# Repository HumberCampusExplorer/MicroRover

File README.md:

# Micro Rover
Adapted from [Rick's Trinket Rover](https://github.com/rwinscot/TrinketRover), estimated build time: 3 hours.

## Table of Contents
1. [Introduction](https://github.com/six0four/MicroRover#1-introduction)
2. [Bill of Materials and Required Tools](https://github.com/six0four/MicroRover#2-bill-of-materials-and-required-tools)
3. [Instructions](https://github.com/six0four/MicroRover#3-instructions)
4. [Future Development](https://github.com/six0four/MicroRover#4-future-development)

## 1. Introduction
A common introduction to microcontrollers is through the [Lego NXT ROBOTC Curriculum](http://www.education.rec.ri.cmu.edu/previews/robot_c_products/teaching_rc_lego_v2_preview/home/ROBOTC_Curriculum_Outline.pdf). This project aims to use a low cost platform to also explore microcontrollers. Similarly, a small rover is assembled as the vehicle. Currently the small rover moves forward until an object reflects infrared light which triggers it to reverse and turn before continuing forward again.

## 2. Bill of Materials and Required Tools
For a list of materials please see the Excel file in the repository.

Regarding tools, the following are a minimum:
- Safety glasses.
- Soldering iron and lead free solder (to be added to materials list).
- Small side cutting pliers.
- Small Phillips screw driver.

## 3. Instructions
1. Soldering guidance:
	1. Start off by watching some ahort soldering guidance videos: [NASA Jove Project](https://radiojove.gsfc.nasa.gov/telescope/soldering.htm).
	2. Continue by watching some [YouTube Videos](https://www.youtube.com/watch?v=BLfXXRfRIzY&list=PLQ32vZrF5U2lFOJTtZDytBWBYVLNp4RYz).
	3. Be sure to wear safety glasses and consult an expert regarding safety, you can even start at your [local hackerspace](https://wiki.hackerspaces.org/List_of_Hackerspaces).
2. Start by programming the trinket with a blink program prior to soldering to make sure it works.
3. Soldering the headers onto to make sure trinket undamaged.
4. Upload the blink program to the trinket again to make sure it is undamaged.
6, Power the trinket from the power supply. Set the current limit.
4. Test the voltage on the 3.7 V 350 mAh Lithium Ion Polymer 552035 Cell. (Notice from the datasheet that the <a href="https://cdn-shop.adafruit.com/product-files/2750/LP552035_350MAH_3.7V_20150906.pdf">Discharge Cut-off
is 3.0V, the Charging Cut-off is 4.2V, and the Storage Voltage is 3.7-3.85V</a>)
7. Turn on the oscilloscope.
8. Turn on the funtion generator.
9. Disconnect the power supply and connect the 
5. Upload the rover code to the trinket.
6.
7.
8.

Fritzing diagrams needed

## 4. Future Development:
- Incorporate multimeter use to check cell.
- Incorporate power supply use as a current controlled alternative to lion cell.
- Incorporate oscilloscope use to view servo motor command signal.
- Incorporate function generator use to create a test control signals.
- Serial communication http://www.ernstc.dk/arduino/tinycom.html to view digitization of infra-red sensor.
- Optimize to stay on desk.
- Optimize to seek dark spaces.
- Optimize for line following.
- Optimize to seek bright spaces and charge via a solar panel.
- Add bluetooth.
- Connect to an Android App that is also connected to Firebase.
- Re-flashing, changing, and removing boot loaders.
- Support for more operating systems.
- Support for more programming languages (Atmel AVR Assembly, ANSI C, Java, Python, IEC 61131-3, javascript, etc.).
- Support for more development environments (AVR-GCC/vi|emacs/AVRdude, Atmel Studio/Visual Studio, etc.).
- Optimize for mapping.
- Communicate with an I2C device as a master
- Communicate with an SPI device.
- Communicate with an I2C device as a slave.
- Communicate with a UART device.
- Communicate via infra-red remote codes.
- Add an H-bridge.
- Add an opto-coupler.
- Add a bidirectional level shifter.
- Modify for DC motors, optical encoders, relays.
- Modify for stepper motors (bipolar and unipolar).
- https://thewanderingengineer.com/2014/08/11/pin-change-interrupts-on-attiny85/
- PID feedback control, fan, thermistor, thermocouple.
- Function generator.
- D to A, PWM.
- A to D, filters.
- Solar cell, photo-resistor.
- Wheatstone bridge, instrumentation amplifier.
- Displays.
- De-bouncing reed switch.
- Emulate a keyboard.
- Playback sound.
- Create a custom PCB with an integrated USB port.
- Shift register, multiplexer.
- RS232, RS485.
- Add a 9-DOF IMU.
- Add MICROCHIP I2C I/O Expander MCP23017.
- Use with http://www.atmel.com/tools/atatmel-ice.aspx and http://www.microchip.com/DevelopmentTools/ProductDetails.aspx?PartNO=ATPOWERDEBUGGER
- Design shell for injection molding.
- Bar/QR code scanners, RFID, magnetic strip, fingerprint readers.
- Add SJA1000/MCP2515 for CAN.
- http://perso.uclouvain.be/fstandae/lightweight_ciphers/
- http://www.instructables.com/id/Optical-Mouse-Odometer-for-Arduino-Robot/?ALLSTEPS
- Currently the project uses a low cost, low power microcontroller from Microchip (Atmel). It could be expanded to be suitable for offerings from other companies such as:
	- Broadcom
	- National Instruments
	- Philips
	- Qualcomm (including NXP, Motorola, and Freescale)
	- Texas Instruments
	- Xilinx
	- Altera
	- Analog Devices
	- Cypress
	- Exynos (Samsung)
	- Infineon Technologies
	- Nordic Semiconductor
	- ON Semiconductor (including Fairchild)
	- Renesas Electronics (including NEC, Hitatchi, Mitsubishi)
	- SGS-THOMSON Microelectronics
	- Silicon Labs

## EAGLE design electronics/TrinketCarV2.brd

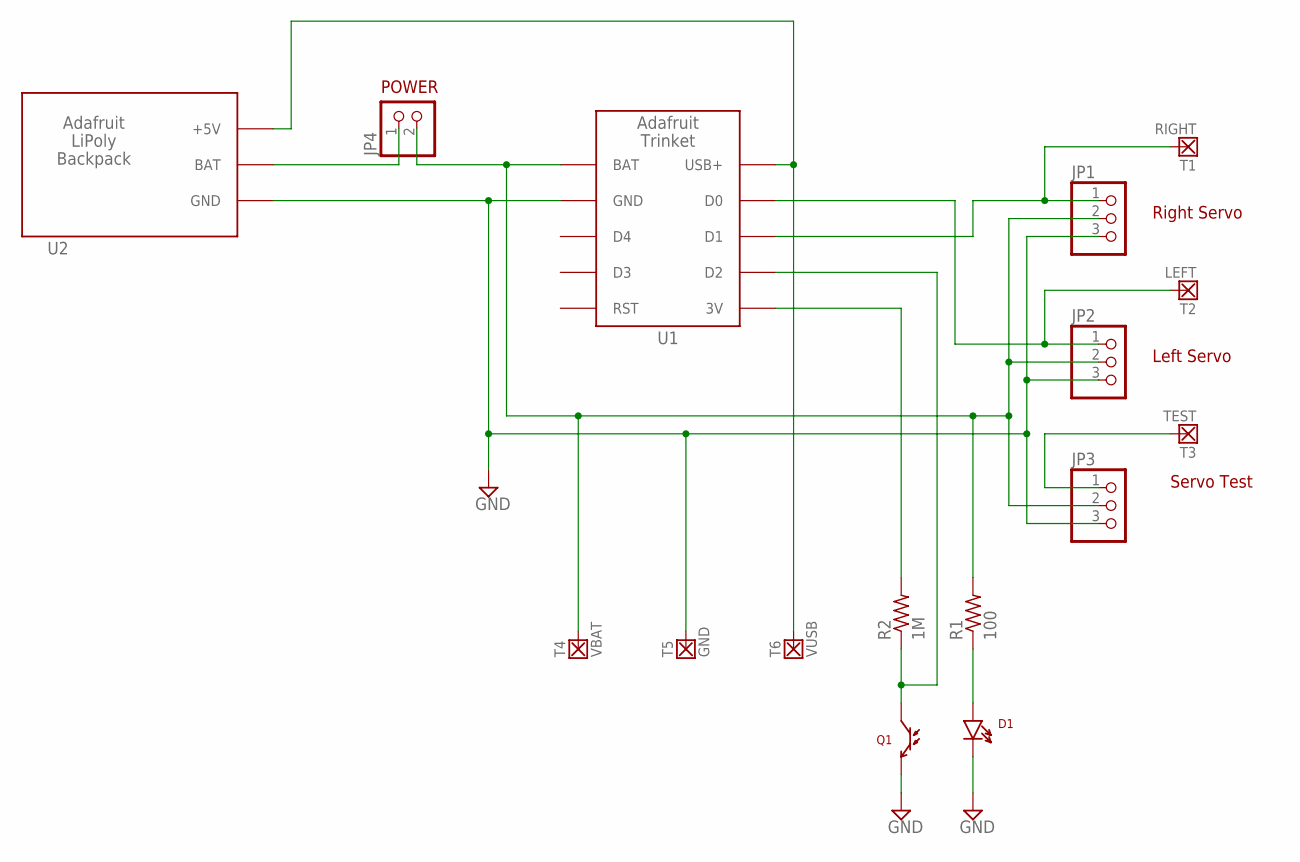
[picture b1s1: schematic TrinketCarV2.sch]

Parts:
D1: LTE-302
JP1, JP2, JP3: PINHD-1X3; 1X03
JP4: PINHD-1X2; 1X02
Q1: LTR-301
R1: 100; 0207/12
R2: 1M; 0207/12
T1: RIGHT; TERMPAD-SMALL
T2: LEFT; TERMPAD-SMALL
T3: TEST; TERMPAD-SMALL
T4: VBAT; TERMPAD-SMALL
T5: GND; TERMPAD-SMALL
T6: VUSB; TERMPAD-SMALL
U1: ADAFRUIT_TRINKET; TRINKITMINI
U2: LIPOLY_BACKPACK; TRINKET_LIPO_BACKPACK

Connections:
GND: D1.C, JP1.3, JP2.3, JP3.3, Q1.E, T5.P$1, U1.P$2 (GND), U2.P$2 (GND)
unnamed: R2.2, U1.P$6 (3V)
unnamed: JP4.1, U2.P$1 (BAT)
unnamed: D1.A, R1.1
unnamed: JP1.1, T1.P$1, U1.P$8 (D1)
unnamed: JP2.1, T2.P$1, U1.P$9 (D0)
unnamed: Q1.C, R2.1, U1.P$7 (D2)
unnamed: JP3.1, T3.P$1
VBAT: JP1.2, JP2.2, JP3.2, JP4.2, R1.2, T4.P$1, U1.P$1 (BAT)
VUSB: T6.P$1, U1.P$10 (USB+), U2.P$3 (+5V)

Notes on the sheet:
Left Servo
Right Servo
Servo Test
POWER

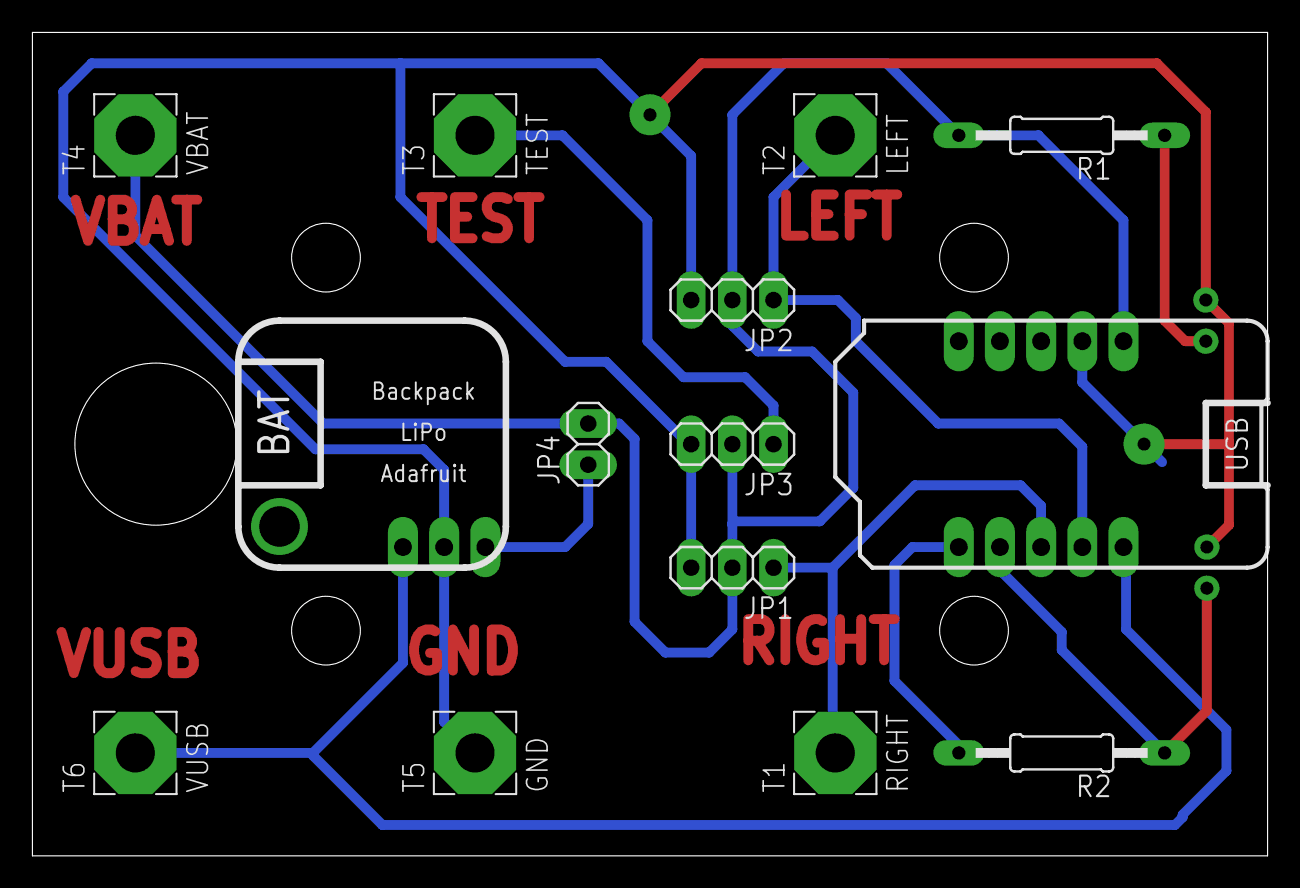
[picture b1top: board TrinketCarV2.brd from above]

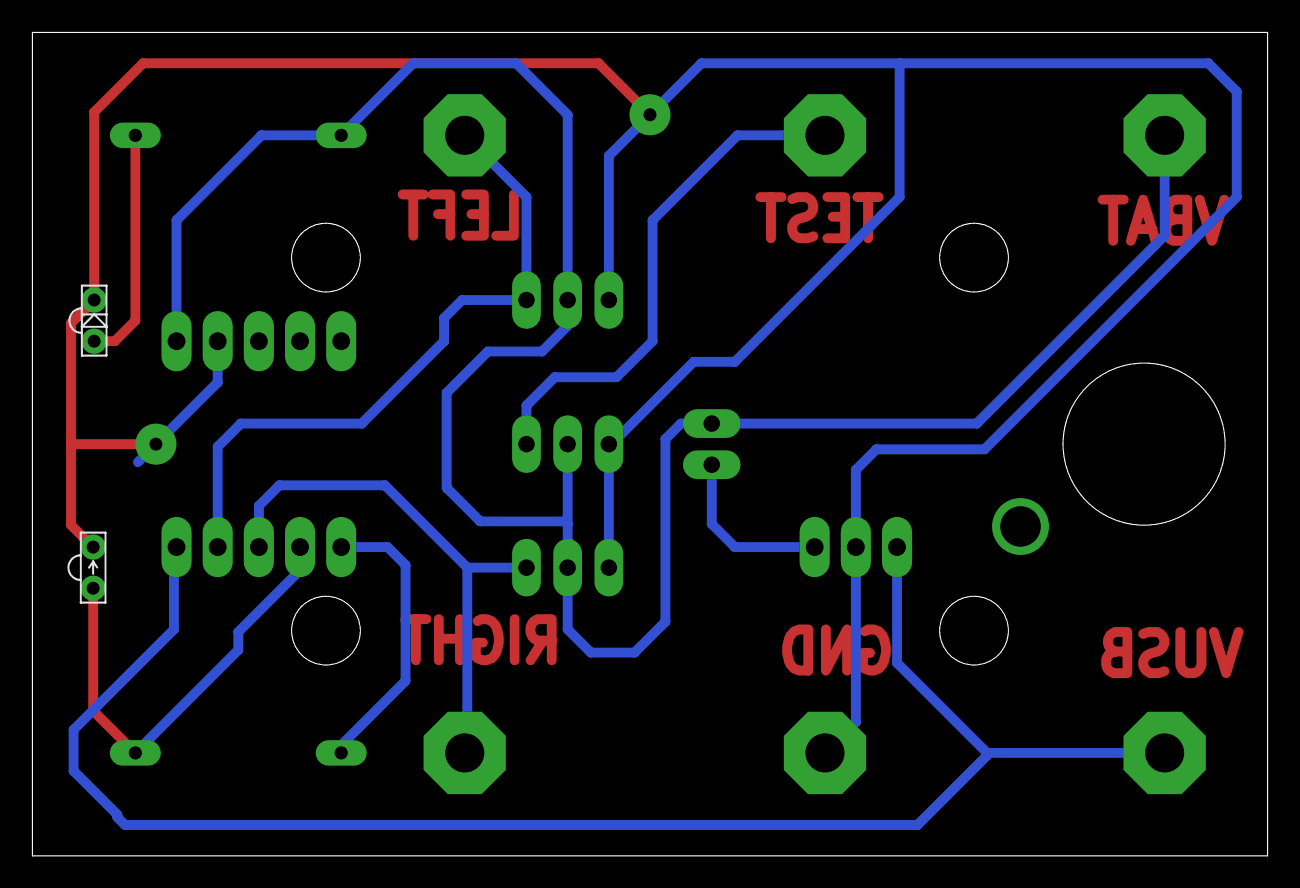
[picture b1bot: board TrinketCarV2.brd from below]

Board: 2 copper layers, 76.2 x 50.8 mm, 16 parts (2 on the bottom side), 10 nets.

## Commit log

2017-04-20 :lollipop: Added .gitattributes & .gitignore files
2017-04-20 Added web framework
2017-04-20 Markdown Formatting
2017-04-20 Framework for instructions
2017-04-20 Needed spaces after the # symbols
2017-04-20 table of contents added
2017-04-20 new lines added
2017-04-20 updating table of contents
2017-04-20 Added photo
2017-04-20 Updated 3D printed parts
2017-04-20 working on inline photo
2017-04-20 added alt text to inline image
2017-04-20 Showing credit to Rick and "fork"
2017-04-20 soldering links
2017-04-20 working on nested list
2017-04-20 Additional plaforms
2017-04-20 Added micro USB cable
2017-04-20 Added notes
2017-04-20 length is adequate
2017-04-21 Added introduction
2017-04-21 Corrected case
2017-04-21 typos corrected
2017-04-21 added ICE
2017-04-21 Added optical tracking instructable link
2017-04-21 Rephrasing of introduction
2017-04-22 Added to future development
2017-04-24 Test equipment use added
2017-04-25 alternate platform companies added
2017-04-25 PLC style programming?
2017-05-03 Added IMU
2017-05-03 Adding PCB info
2017-05-03 Testing Ohm symbol
2017-05-03 Updated section number
2017-05-03 Ohm symbol correct
2017-05-04 Early Adopter Instructions started
2017-05-04 EarlyAdopterKit
2017-05-04 lead free
2017-05-04 link correction
2017-05-04 Added wheels
2017-05-04 Starting assembly instructions
2017-05-04 Renaming Kelly's photos
2017-05-04 Order modified
2017-05-05 Jeremy started
2017-05-05 Added PCB
2017-05-08 Added bookstore video
2017-05-08 Added unboxing video
2017-05-08 added parts
2017-05-08 Resistor ID cards added
2017-05-08 Adding network architecture
2017-05-08 Working on introduction
2017-05-08 Spelling and formating
2017-05-08 additional formatting changes
2017-05-08 Added link to sockets image
2017-05-08 Updated format
2017-05-08 USB cables are in!
2017-05-09 Added image of completed rover
2017-05-09 typo correction
2017-05-09 reordering of list
2017-05-09 inserted USB cable image
2017-05-09 added more images for soldering clarity
2017-05-09 Next will be via and firmware
2017-05-09 lab photos added
2017-05-09 turret photos added
2017-05-09 turret placement images placed inline
2017-05-09 added chassis
2017-05-09 moved parts made here to top of list
2017-05-09 cutting time added
2017-05-11 Adding images
2017-05-12 added aervo photos
2017-05-12 Adding menu items
2017-05-13 Adding mechanical assembly
2017-05-13 Updating mechanical assembly instructions
2017-05-14 Adding test equipment inline images
2017-05-14 Adding inline test equipment files
2017-05-14 Added function generator and oscilloscope use
2017-05-14 Adding over current protection images
2017-05-14 Test euipment use is part of soldering section
2017-05-14 Over current photos linked
2017-05-14 Leads should not attached during set up
2017-05-14 Showing power connection for servo
2017-05-14 Inline images for servo power
2017-05-14 More inline images for servo power
2017-05-15 Spelling corrections
2017-05-15 Charging with power supply
2017-05-15 Function generator, oscilloscope, and power
2017-05-15 Muhammad tweaked my brain that I forgot to port some instructions from the markdown file
2017-05-15 Charging photo order improved
2017-05-15 Increase in current to not trip on servo
2017-05-15 Added test points
2017-05-15 Default Setup added for Oscilloscope
2017-05-15 Adding Brandeen's photos
2017-05-15 tag correction
2017-05-15 broken image link
2017-05-15 extra period in filename
2017-05-24 Starting to consider a group buy
2017-05-30 Parts list updated to allow for shipping costs to be included
2017-06-19 Sink location correction
2017-12-11 Images added

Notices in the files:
parts and their libraries:
SparkFun-Sensors: Licensing: Creative Commons ShareAlike 4.0 International - https://creativecommons.org/licenses/by-sa/4.0
